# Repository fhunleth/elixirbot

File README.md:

# ElixirBot

## Parts

The following lists all of the parts except for the laser cut frame and 3D
printed ball bearing holder. If you have a local hackerspace or Fab Lab, you're
in luck. If not, companies like Pololu and Ponoko will do it for you, but I have
not tested the designs with either of them.

  - Raspberry Pi Model A+ - $20
  - Pi Camera - $30
  - 2 [Spring RC SM-S4303R Servos](https://www.pololu.com/product/1248) - $26
  - WiFi dongle
  - [Daughter board PCB](https://oshpark.com/shared_projects/lCHfJqx6) - $3
  - [Pololu 5V Step-Up/Step-Down Voltage Regulator S7V7F5](https://www.pololu.com/product/2119) - $5
  - [4-AA Battery Holder](https://www.pololu.com/product/1153) - $1
  - [8-pin DIP socket](http://www.digikey.com/product-detail/en/A08-LC-TT/AE9986-ND/821740)
  - [10 position socket](http://www.digikey.com/product-detail/en/61301021821/732-2861-ND/2508630)
  - [2 position, 2.54 mm terminal block](http://www.digikey.com/product-detail/en/OSTVN02A150/ED10561-ND/1588862)
  - [ATtiny85](http://www.digikey.com/product-detail/en/ATTINY85-20PU/ATTINY85-20PU-ND/735469) - $2
  - [16 mm ball bearing](http://www.mcmaster.com/#9292k53/=w80vpw) - $1
  - [3/8" #6 pan head screws](http://www.mcmaster.com/#90190a146/=w80x6q)
  - [3/8" #4 pan head screws](http://www.mcmaster.com/#90190a103/=w80y2f)
  - [7/16" 4-40 F-F standoffs](https://www.pololu.com/category/114/female-female-standoffs)
  - [5/16" 4-40 machine screws](https://www.pololu.com/product/1961)
  - [4-40 machine hex nuts](https://www.pololu.com/product/1068)
  - [2-56 machine hex nuts](https://www.pololu.com/product/1067)
  - [5/16" 2-56 machine screws](https://www.pololu.com/product/1956)
  - [.1" header header]()
  - [.1" short]()
  - [10K resister 0805 package]()
  - [.1 uF capacitor 0805 package]()
  - MicroSD card
  - Rechargable AA batteries - Eneloop or other ~2000 mAh batteries

Very useful items:

  - [3V FTDI cable](https://www.sparkfun.com/products/9717)

## Building the frame

The robot frame is a modification of the awesome [SumoBot
Jr.](http://sumobotkit.com). I've made the following modifications to the
original design:

  1. Changed screw hole locations to mount a Raspberry Pi Model A
  2. Added a mount for a Pi Camera up front
  3. Added more room for batteries and enlarged the servo hole slightly
  4. Modified the wheels to screw into the servo horn rather than directly
     attaching (not completely sure that this is an improvement)

The `dxf` containing the laser cutter pattern was created in
[QCad](http://qcad.org). I cut the pattern in 5 mm birch plywood using a Full
Spectrum laser cutter. The Full Spectrum driver isn't smart about which lines to cut
first like the Epilog and Universal Laser drivers, so it has the cuts divided
into "first" and "second" passes.

## Building the electronics

First, order a PCB from [OSH Park](https://oshpark.com/shared_projects/lCHfJqx6).

IMPORTANT: I messed up the drill size for the 4-40 mounts, so the mounting holes
on the daughterboard need to be manually enlarged with a 7/64" drill bit. Don't
worry, I left clearance.

Solder the surface mount parts first. For the 10K resisters, make sure that you
have the orientation correct (same direction as silkscreen label). You'll see
what I mean.

The remaining components are fairly straightforward to solder since they're
through-hole. I didn't solder in the ISP connector, since I programmed the
ATtiny85 chips before plugging them into the board.

See the [ATtiny85 program](https://github.com/fhunleth/elixirbot/blob/master/hw/bot_attiny_controller/bot_attiny_controller.ino)
for build and programming instructions.

## Building

  1. Build a `nerves_rpi_elixirbot_defconfig` configuration of Nerves
  2. `. ./nerves-env.sh` in the Nerves directory
  3. Go here and run `make`

## Post-mortem

One thing I learned on this project was that the Raspberry Pi does not support
clock stretching on the I2C bus. Apparently, this was well documented, but I
hadn't seen it beforehand. The I2C code on the ATtiny85 does stretch the clock,
so if you rebuild this exactly, you will see I2C errors. With work, it may be
possible to fix the clock stretching issue, but if I were to do this project
again, I would look at another part besides the ATtiny85 or see if the RPi's PWM
support is improved.

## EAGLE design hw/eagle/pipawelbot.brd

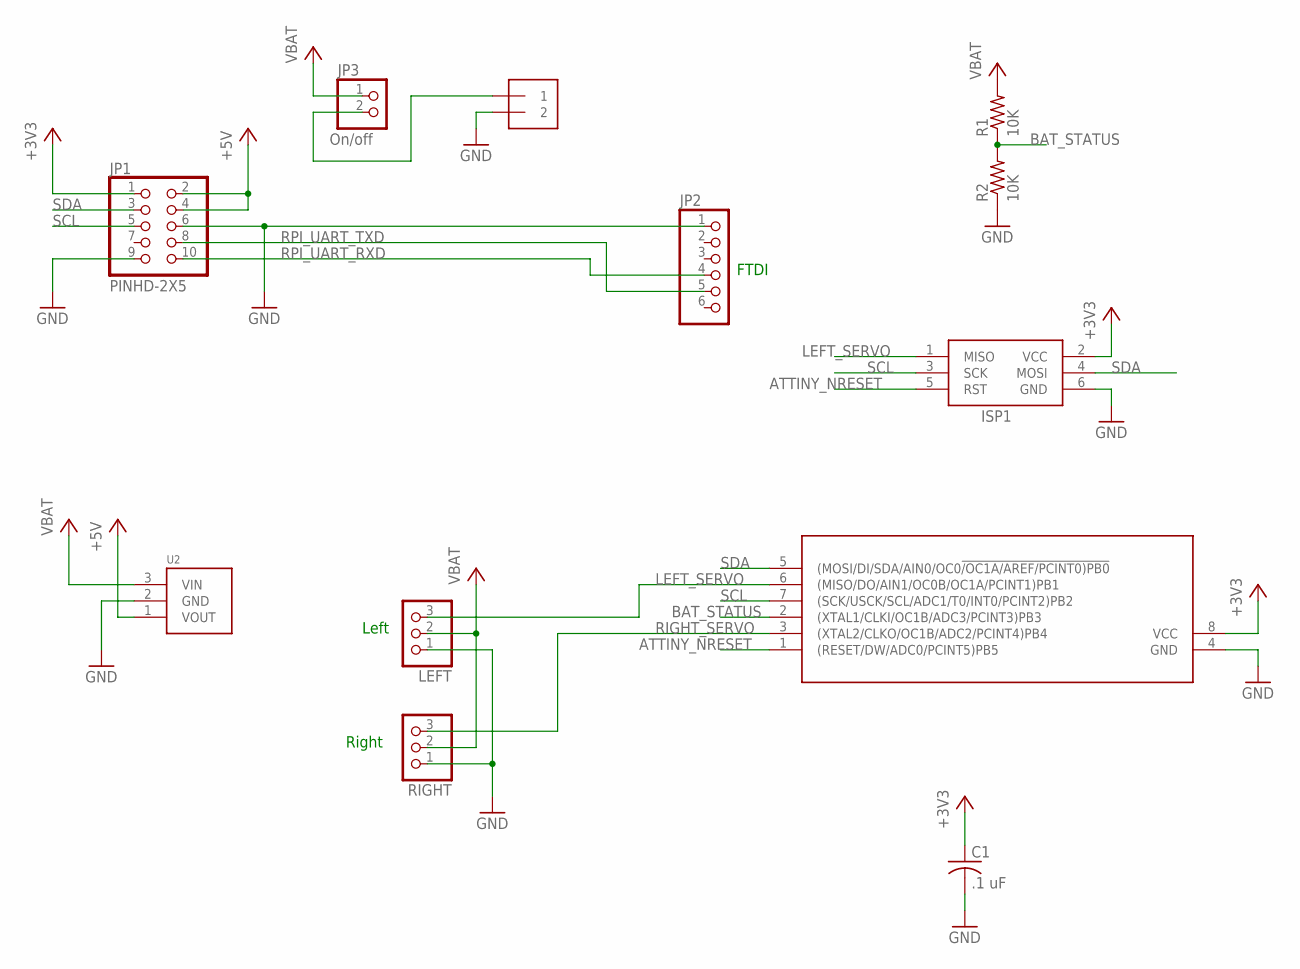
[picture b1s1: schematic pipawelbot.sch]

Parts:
C1: .1 uF; C0805
ISP1: AVRISP-6; AVRISP
J1: TERMINAL_BLOCK_1X2-2.54MM; TERMINAL_BLOCK-1X2-0.1
JP1: PINHD-2X5; 2X5
JP2: PINHD-1X6; 1X06
JP3: PINHD-1X2; 1X02
LEFT: PINHD-1X3; 1X03
R1, R2: 10K; R0805
RIGHT: PINHD-1X3; 1X03
U1: ATTINY85; DIL08
U2: S7V7F5; POLOLU-REG

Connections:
+3V3: C1.1, ISP1.2 (VCC), JP1.1, U1.8 (VCC)
+5V: JP1.2, JP1.4, U2.1 (VOUT)
ATTINY_NRESET: ISP1.5 (RST), U1.1 ((RESET/DW/ADC0/PCINT5)PB5)
BAT_STATUS: R1.1, R2.2, U1.2 ((XTAL1/CLKI/OC1B/ADC3/PCINT3)PB3)
GND: C1.2, ISP1.6 (GND), J1.1 (2), JP1.6, JP1.9, JP2.1, LEFT.1, R2.1, RIGHT.1, U1.4 (GND), U2.2 (GND)
LEFT_SERVO: ISP1.1 (MISO), LEFT.3, U1.6 ((MISO/DO/AIN1/OC0B/OC1A/PCINT1)PB1)
RIGHT_SERVO: RIGHT.3, U1.3 ((XTAL2/CLKO/OC1B/ADC2/PCINT4)PB4)
RPI_UART_RXD: JP1.10, JP2.4
RPI_UART_TXD: JP1.8, JP2.5
SCL: ISP1.3 (SCK), JP1.5, U1.7 ((SCK/USCK/SCL/ADC1/T0/INT0/PCINT2)PB2)
SDA: ISP1.4 (MOSI), JP1.3, U1.5 ((MOSI/DI/SDA/AIN0/OC0!/OC1A/AREF/PCINT0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)
VBAT_IN: J1.2 (1), JP3.2
VCC: JP3.1, LEFT.2, R1.2, RIGHT.2, U2.3 (VIN)

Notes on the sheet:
Left
Right
FTDI
On/off

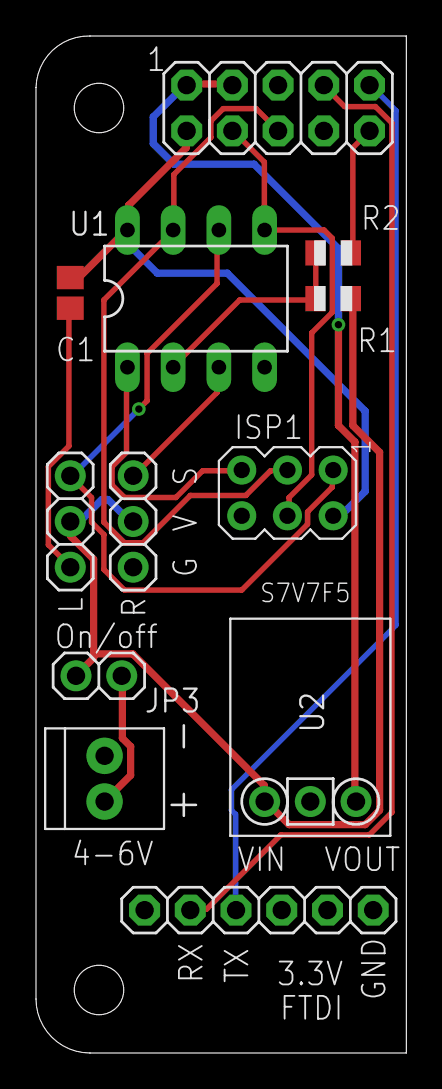
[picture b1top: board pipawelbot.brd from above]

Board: 2 copper layers, 20.6 x 56.5 mm, 12 parts (0 on the bottom side), 13 nets.

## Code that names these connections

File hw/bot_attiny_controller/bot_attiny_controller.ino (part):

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 *
 * Pin   Function
 * 1     NRESET
 * 2     PB3 - Battery level/2 * 3.3/255
 * 3     PB4 - Right servo (OC1B)
 * 4     GND
 * 5     PB0 - I2C SDA
 * 6     PB1 - Left servo (OC1A)
 * 7     PB2 - I2C SCL
 * 8     VCC (+3.3V)
 */

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
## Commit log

2015-02-28 Latest updates - hacks, but signs of life
2015-02-28 Direction fixes for weird servo
2015-02-28 Flip horizontally too
2015-02-28 Add laser cut outlines
2015-03-02 Add Eagle files for daughterboard
2015-03-03 Add picture
2015-03-03 Missed one JSEX->JSX
2015-03-07 Add more docs and tiny bootloader
2015-03-08 Much improved ATtiny firmware
2015-03-08 Add lots more instructions, BOM, and cleanup
2015-03-17 Latest updates to laser cut images
    Cuts well on 45W Full Spectrum Laser on 5mm plywood
2015-03-17 Move generic Makefile parts to main Nerves repo
2015-03-17 Remove overlapping lines on camera holder
2015-03-17 Color for Elixir shell
2015-03-20 Updates for EF15
2015-03-22 Final testing
2015-11-24 Add post-mortem notes
